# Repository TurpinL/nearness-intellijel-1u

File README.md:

# Nearness-Intellijel 1U

This is an adaption of [sonocircuit's nearness module 1u adaptation](https://github.com/sonocircuit/Nearness-1U) (Which itself is an 1u adaptation of [sarnesjo's nearness module](https://github.com/sarnesjo/nearness)) now in 1U Intellijel format. 

### Changes made:

- The back PCB is now 22.5mm high to fit Intellijel's spec
- Rearranged jacks, new faceplate
- 14hp
- Slightly adjusted resistor values based on availiability 

## Making your own

[Digikey BOM](https://www.digikey.com.au/en/mylists/list/PDI5ANLO88) **Note**: 3 pin header, 2x5 pin IDC Box header and jacks not included.

**WARNING**: I haven't yet assembled one of these to test it, there may be errors in and or all components of this. Build at your own risk!

**WARNING**: Watch out for the 3 pin header. It has to be soldered before the jacks, otherwise it's pads are inaccessible. You'll also want to trim its leads so they don't stick too far out the back of the PCB. It's best if the resulting solder mound is flat or recessed, otherwise it risks shorting out in the jack and/or the jack not sitting flat.

## Licence

Thanks to sarnesjo and sonocircuit for sharing! Same licence applies.

[CC BY-SA 4.0](http://creativecommons.org/licenses/by-sa/4.0/)

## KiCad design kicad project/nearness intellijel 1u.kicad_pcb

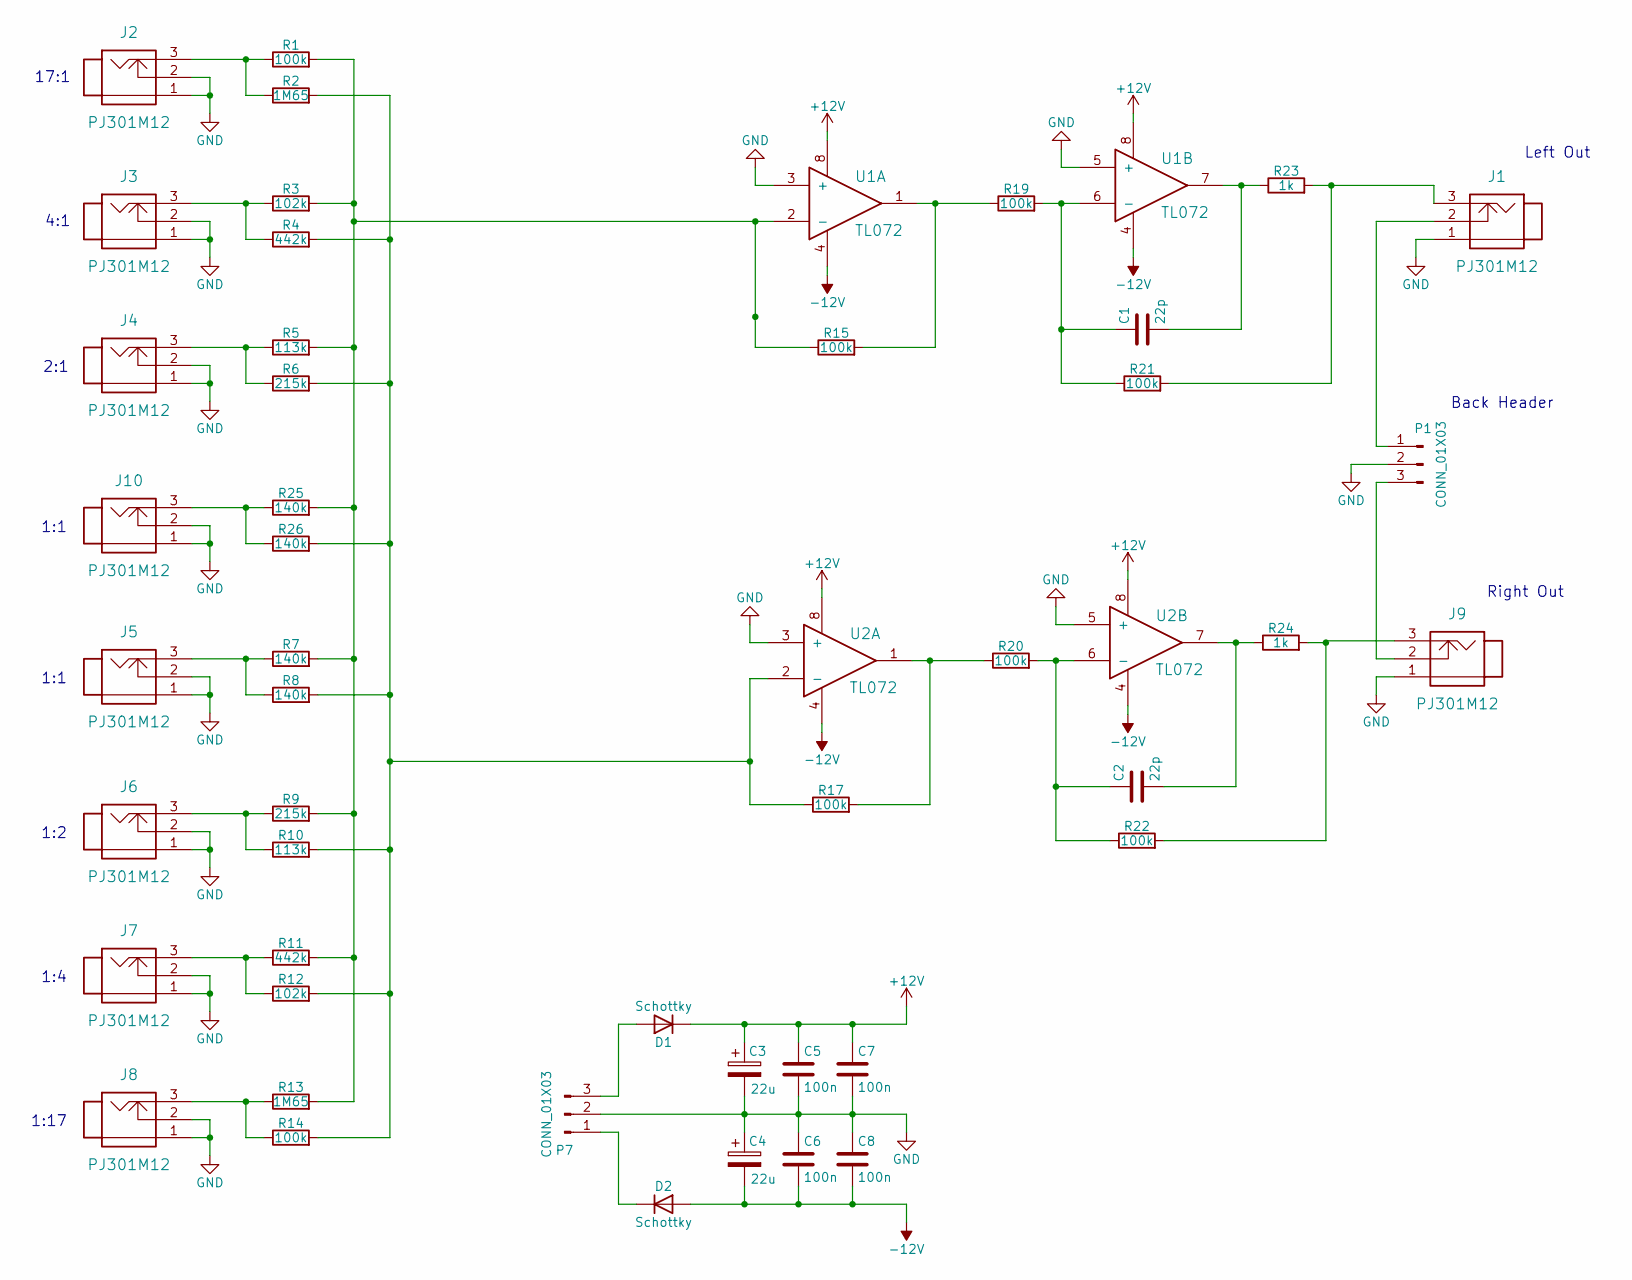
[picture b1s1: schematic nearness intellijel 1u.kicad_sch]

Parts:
C1, C2: 22p; C_1206_3216Metric_Pad1.33x1.80mm_HandSolder
C3, C4: 22u; CP_Radial_D5.0mm_P2.00mm
C5, C6, C7, C8: 100n; C_1206_3216Metric_Pad1.33x1.80mm_HandSolder
D1, D2: Schottky; D_SOD-323_HandSoldering
J1, J2, J3, J4, J5, J6, J7, J8, J9, J10: PJ301M12
P1: CONN_01X03; Pin_1x3
P7: CONN_01X03; IDC-Header_2x05_P2.54mm_Vertical
R1, R14, R15, R17, R19, R20, R21, R22: 100k; R_1206_3216Metric_Pad1.30x1.75mm_HandSolder
R2, R13: 1M65; R_1206_3216Metric_Pad1.30x1.75mm_HandSolder
R3, R12: 102k; R_1206_3216Metric_Pad1.30x1.75mm_HandSolder
R4, R11: 442k; R_1206_3216Metric_Pad1.30x1.75mm_HandSolder
R5, R10: 113k; R_1206_3216Metric_Pad1.30x1.75mm_HandSolder
R6, R9: 215k; R_1206_3216Metric_Pad1.30x1.75mm_HandSolder
R7, R8, R25, R26: 140k; R_1206_3216Metric_Pad1.30x1.75mm_HandSolder
R23, R24: 1k; R_1206_3216Metric_Pad1.30x1.75mm_HandSolder
U1, U2: TL072; SOIC-8

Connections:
+12V: C3.1, C5.1, C7.1, D1.1 (K), U1.8, U2.8
-12V: C4.2, C6.2, C8.2, D2.2 (A), U1.4, U2.4
GND: C3.2, C4.1, C5.2, C6.1, C7.2, C8.1, J1.1, J2.1, J2.2, J3.1, J3.2, J4.1, J4.2, J5.1, J5.2, J6.1, J6.2, J7.1, J7.2, J8.1, J8.2, J9.1, J10.1, J10.2, P1.2, P7.2, U1.3 (+), U1.5 (+), U2.3 (+), U2.5 (+)
unnamed: C1.2, R23.1, U1.7
unnamed: C2.2, R24.1, U2.7
unnamed: D1.2 (A), P7.3
unnamed: D2.1 (K), P7.1
unnamed: J1.3, R21.2, R23.2
unnamed: J2.3, R1.1, R2.1
unnamed: J3.3, R3.1, R4.1
unnamed: J4.3, R5.1, R6.1
unnamed: J5.3, R7.1, R8.1
unnamed: J6.3, R9.1, R10.1
unnamed: J7.3, R11.1, R12.1
unnamed: J8.3, R13.1, R14.1
unnamed: J9.3, R22.2, R24.2
unnamed: J10.3, R25.1, R26.1
unnamed: J1.2, P1.1
unnamed: J9.2, P1.3
unnamed: R15.2, R19.1, U1.1
unnamed: R17.2, R20.1, U2.1
unnamed: R1.2, R3.2, R5.2, R7.2, R9.2, R11.2, R13.2, R15.1, R25.2, U1.2 (-)
unnamed: C1.1, R19.2, R21.1, U1.6 (-)
unnamed: R2.2, R4.2, R6.2, R8.2, R10.2, R12.2, R14.2, R17.1, R26.2, U2.2 (-)
unnamed: C2.1, R20.2, R22.1, U2.6 (-)

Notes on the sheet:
2:1
1:4
1:1
4:1
Right Out
Left Out
17:1
1:2
1:17
Back Header

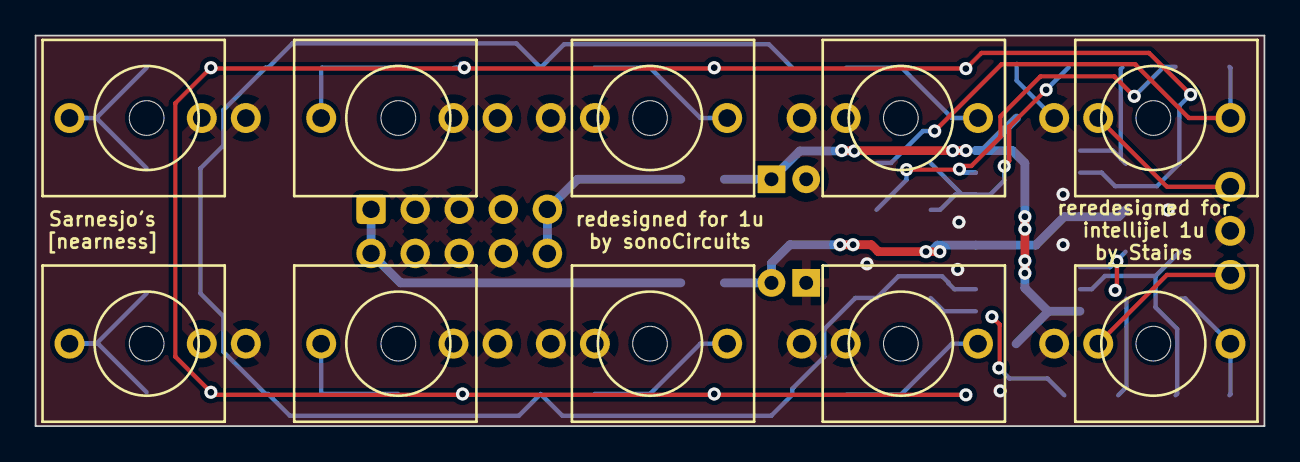
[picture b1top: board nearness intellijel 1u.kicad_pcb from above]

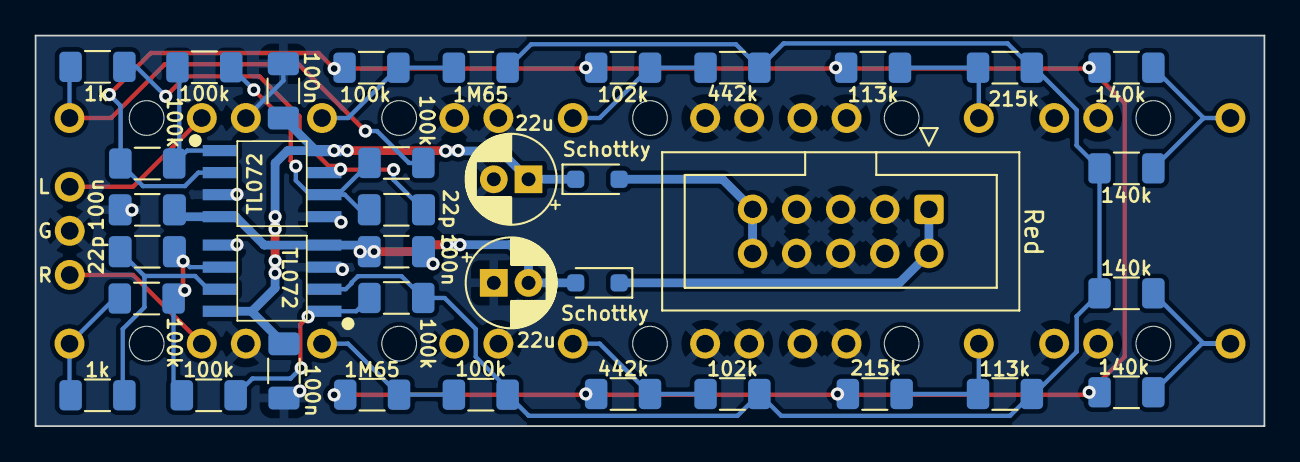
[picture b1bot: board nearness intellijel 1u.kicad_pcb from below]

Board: 2 copper layers, 70.8 x 22.5 mm, 48 parts (38 on the bottom side), 25 nets.

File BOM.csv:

#,Reference,Qty,Value,Footprint,Source
1,"C1, C2",2,22p,Capacitor_SMD:C_1206_3216Metric_Pad1.33x1.80mm_HandSolder,https://www.digikey.com.au/en/products/detail/w%C3%BCrth-ele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
2,"C3, C4",2,22u,Capacitor_THT:CP_Radial_D5.0mm_P2.00mm,https://www.digikey.com.au/en/products/detail/panasonic-elec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
3,"C5, C6, C7, C8",4,100n,Capacitor_SMD:C_1206_3216Metric_Pad1.33x1.80mm_HandSolder,https://www.digikey.com.au/en/products/detail/kemet/C1206C10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
4,"D1, D2",2,Schottky,Diode_SMD:D_SOD-323_HandSoldering,https://www.digikey.com.au/en/products/detail/toshiba-semico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
5,"J1, J2, J3, J4, J5, J6, J7, J8, J9, J10",10,PJ398SM,nearness: PJ398SM,https://www.thonk.co.uk/shop/thonkiconn/
6,P1,1,CONN_01X03,nearness:Pin_1x3,
7,P7,1,CONN_01X03,Connector_IDC:IDC-Header_2x05_P2.54mm_Vertical,
8,"R1, R14, R15, R17, R19, R20, R21, R22",8,100k,Resistor_SMD:R_1206_3216Metric_Pad1.30x1.75mm_HandSolder,https://www.digikey.com.au/en/products/detail/stackpole-elec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
9,"R2, R13",2,1M65,Resistor_SMD:R_1206_3216Metric_Pad1.30x1.75mm_HandSolder,https://www.digikey.com.au/en/products/detail/vishay-dale/CR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
10,"R3, R12",2,102k,Resistor_SMD:R_1206_3216Metric_Pad1.30x1.75mm_HandSolder,https://www.digikey.com.au/en/products/detail/stackpole-elec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
11,"R4, R11",2,442k,Resistor_SMD:R_1206_3216Metric_Pad1.30x1.75mm_HandSolder,https://www.digikey.com.au/en/products/detail/yageo/RC1206FR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
12,"R5, R10",2,113k,Resistor_SMD:R_1206_3216Metric_Pad1.30x1.75mm_HandSolder,https://www.digikey.com.au/en/products/detail/vishay-dale/CR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
13,"R6, R9",2,215k,Resistor_SMD:R_1206_3216Metric_Pad1.30x1.75mm_HandSolder,https://www.digikey.com.au/en/products/detail/yageo/RC1206FR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
14,"R7, R8, R25, R26",4,140k,Resistor_SMD:R_1206_3216Metric_Pad1.30x1.75mm_HandSolder,https://www.digikey.com.au/en/products/detail/yageo/RC1206FR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
15,"R23, R24",2,1k,Resistor_SMD:R_1206_3216Metric_Pad1.30x1.75mm_HandSolder,https://www.digikey.com.au/en/products/detail/stackpole-elec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
16,"U1, U2",2,TL072,nearness:SOIC-8,https://www.digikey.com.au/en/products/detail/texas-instrume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

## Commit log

2023-11-22 Adjusted resistor values
2023-12-22 Fixed BOM link
2024-01-01 Fixed hole sizes and mislabeled component
